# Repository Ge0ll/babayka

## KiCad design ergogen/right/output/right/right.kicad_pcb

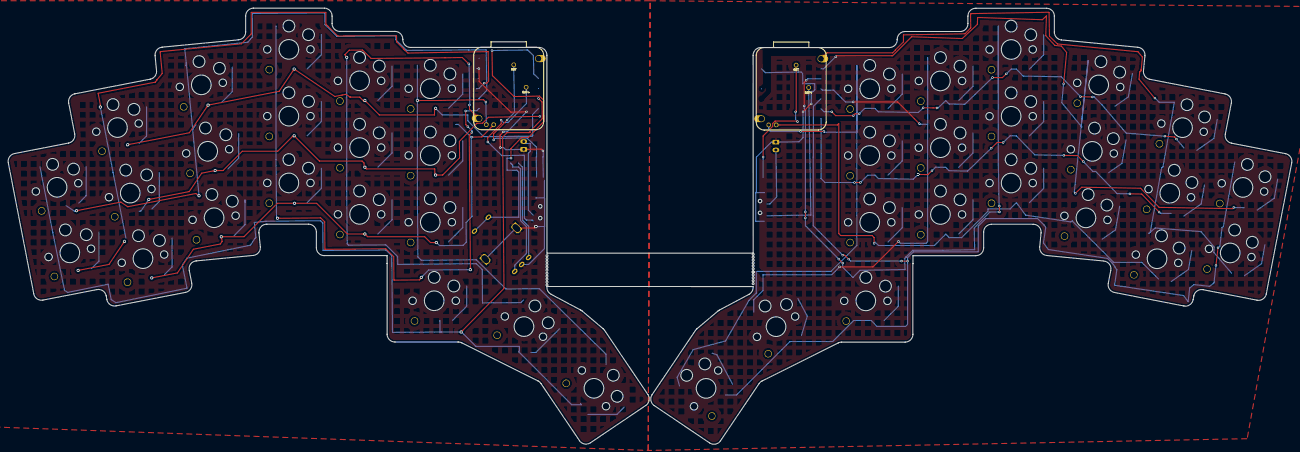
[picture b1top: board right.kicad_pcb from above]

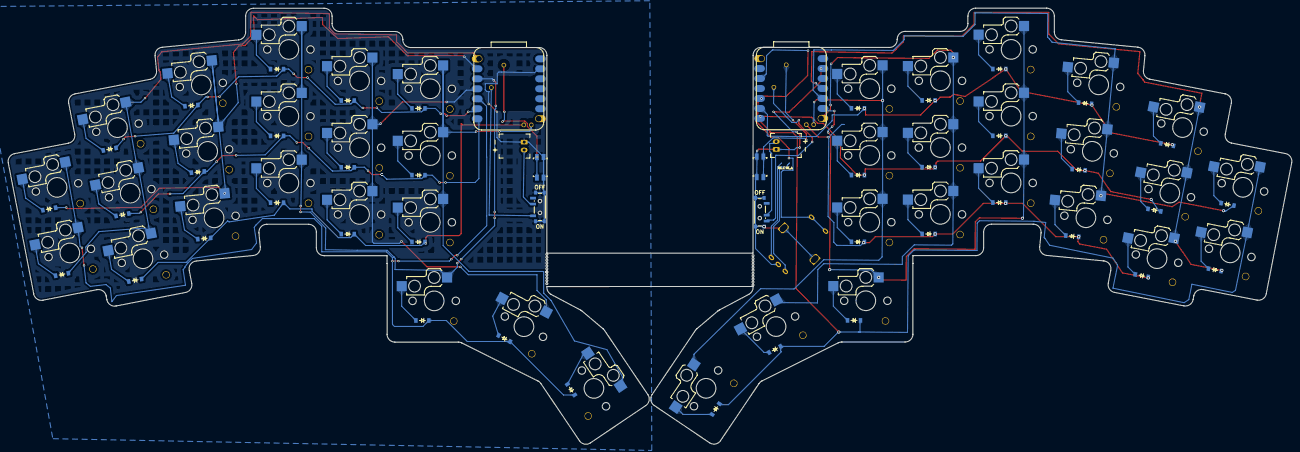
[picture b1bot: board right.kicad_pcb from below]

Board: 2 copper layers, 326.8 x 111.0 mm, 89 parts (86 on the bottom side), 54 nets.

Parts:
D1, D2, D3, D4, D5, D6, D7, D8, D9, D10, D11, D12, D13, D14, D15, D16, D17, D18, D19, D20, D21, D22, D23, D24, D25, D26, D27, D28, D29, D30, D31, D32, D33, D34, D35, D36, D37, D38, D39, D40: diode_tht_sod123
JST1, JST1#2: battery_connector_jst_ph_2
PWR1, PWR1#2: power_switch_smd_side
RE1: rotary_encoder_ec11_ec12
RST1, RST1#2: reset_switch_smd_side
S1, S2, S3, S4, S5, S6, S7, S8, S9, S10, S11, S12, S13, S14, S15, S16, S17, S18, S19, S20, S21, S22, S23, S24, S25, S26, S27, S28, S29, S30, S31, S32, S33, S34, S35, S36, S37, S38, S39, S40: switch_choc_v1_v2
U?: xiao-ble-thruhole; xiao-pogo-rev
U?#2: xiao-ble-thruhole; xiao-pogo-rev

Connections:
BAT_P: PWR1.3, PWR1#2.1, U?.BAT_P, U?#2.BAT_P
GND: JST1.1, JST1#2.1, RE1.B, RST1.1, RST1.3, RST1#2.1, RST1#2.3
P0: D19.1, D39.1, S1.1, S2.1, S3.1, S21.1, S22.1, S23.1
P1: D20.1, D40.1, S4.1, S5.1, S6.1, S24.1, S25.1, S26.1
P2: S7.1, S8.1, S9.1, S16.1, S27.1, S28.1, S29.1, S36.1
P3: S10.1, S11.1, S12.1, S17.1, S30.1, S31.1, S32.1, S37.1
P4: S13.1, S14.1, S15.1, S18.1, S33.1, S34.1, S35.1, S38.1
P5: D1.1, D4.1, D7.1, D10.1, D13.1, D21.1, D24.1, D27.1, D30.1, D33.1
P6: D2.1, D5.1, D8.1, D11.1, D14.1, D22.1, D25.1, D28.1, D31.1, D34.1
P7: D3.1, D6.1, D9.1, D12.1, D15.1, D23.1, D26.1, D29.1, D32.1, D35.1
P8: D16.1, D17.1, D18.1, D36.1, D37.1, D38.1, S19.1, S20.1, S39.1, S40.1
P10: RE1.S1, RE1.S2
RAW: JST1.2, JST1#2.2, PWR1.2, PWR1#2.2
RST: RST1.2, RST1.4, RST1#2.2, RST1#2.4, U?.18, U?#2.18
far_thumb: D18.2, S18.2
home_thumb: D17.2, S17.2
index_bottom: D10.2, S10.2
index_home: D11.2, S11.2
index_top: D12.2, S12.2
inner_bottom: D13.2, S13.2
inner_home: D14.2, S14.2
inner_top: D15.2, S15.2
middle_bottom: D7.2, S7.2
middle_home: D8.2, S8.2
middle_top: D9.2, S9.2
mirror_far_thumb: D38.2, S38.2
mirror_home_thumb: D37.2, S37.2
mirror_index_bottom: D30.2, S30.2
mirror_index_home: D31.2, S31.2
mirror_index_top: D32.2, S32.2
mirror_inner_bottom: D33.2, S33.2
mirror_inner_home: D34.2, S34.2
mirror_inner_top: D35.2, S35.2
mirror_middle_bottom: D27.2, S27.2
mirror_middle_home: D28.2, S28.2
mirror_middle_top: D29.2, S29.2
mirror_near_thumb: D36.2, S36.2
mirror_pinky2_extra1: D39.2, S39.2
mirror_pinky2_extra2: D40.2, S40.2
mirror_pinky_bottom: D21.2, S21.2
mirror_pinky_home: D22.2, S22.2
mirror_pinky_top: D23.2, S23.2
mirror_ring_bottom: D24.2, S24.2
mirror_ring_home: D25.2, S25.2
mirror_ring_top: D26.2, S26.2
near_thumb: D16.2, S16.2
pinky2_extra1: D19.2, S19.2
pinky2_extra2: D20.2, S20.2
pinky_bottom: D1.2, S1.2
pinky_home: D2.2, S2.2
pinky_top: D3.2, S3.2
ring_bottom: D4.2, S4.2
ring_home: D5.2, S5.2
ring_top: D6.2, S6.2

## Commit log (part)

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2025-12-22 footprints
2025-12-26 test
2025-12-26 fixes
2026-01-05 right side development
2026-01-28 Initial plan
